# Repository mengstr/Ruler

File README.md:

# PCB Ruler

This is a draft of the kind of ruler I'd be interested in. It's not only a device for determinig suitable holes for parts but also showcases the capabilities of the fab and the limits of the basic/simple class of service.

### Ruler
- mm and inch (1/16th) measurement (or else it wouldn't be a ruler)

### Holes, plated and unplated
- Holes 0.5-1.4 mm for testing component lead sizes
- Holes 1.9-2.3 mm for M2 screws
- Holes 2.9-3.9 mm for 3mm LED and tactile switches on front panels. Also M3
- Holes 4.9-5.5 mm for 5mm LED

### Fonts
- Test of regular font sizes
- Test of inverted "Buzzard" font sizes

### Slots
- Plated slots for USB-C
- 1.8mm unplated slot with solder tabs for testing two PCBs joined 90 degrees
- 2.4mm unplated slot for...

### Naked HASL quality
- Test for solderbridges at soldermaskless traces for 200/150 200/200 200/300um

### Silkscreen resolution
- Test grid at 0.15 and 0.20 mm tracewidth/pitch

### Solderdams
- Availability of solder dams at 0.4, 0.5, 0.65 and 1.27 pitch tssop/soic

### Transparency of soldermask
- Test text on copper respective non-copper

### Transparency of naked FR-4 material
- Test transpareny for backlit LED indicators

### Quality tented vias
- How much soldermask and silkscreen will be applied

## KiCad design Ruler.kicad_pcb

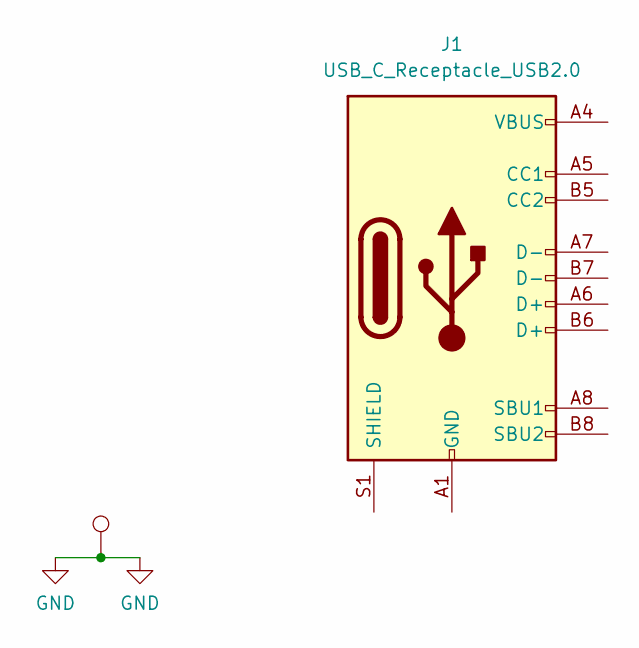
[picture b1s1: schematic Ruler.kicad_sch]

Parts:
J1: USB_C_Receptacle_USB2.0; USB_C_Receptacle_Palconn_UTC16-G
TP1: TestPoint; TestPoint_Pad_1.0x1.0mm

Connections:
GND: TP1.1
unnamed: J1.A1 (GND), J1.A12 (GND), J1.B1 (GND), J1.B12 (GND)
unnamed: J1.A4 (VBUS), J1.A9 (VBUS), J1.B4 (VBUS), J1.B9 (VBUS)

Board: 2 copper layers, 7 parts (1 on the bottom side), 2 nets, no tracks yet.

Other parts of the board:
kibuzzard-64B6E5A6: G***; kibuzzard-64B6E5A6
kibuzzard-64B6E5BD: G***; kibuzzard-64B6E5BD
kibuzzard-64B6E5EB: G***; kibuzzard-64B6E5EB
kibuzzard-64B6E591: G***; kibuzzard-64B6E591
kibuzzard-64B6E609: G***; kibuzzard-64B6E609

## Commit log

2023-07-18 Add Images
2023-07-19 Added vias and transparency
2023-07-19 Fix soldermask pullback on vias
2023-07-20 Add custome bridges
2023-10-22 Update for Twitter giveaway
2023-10-22 Remove backups
2023-10-22 Change to real image of Twitter Ruler
2023-10-22 Fix filename
